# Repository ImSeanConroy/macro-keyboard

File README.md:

# Minimal Layout, Maximum Efficiency

A collection of macro keyboards to boost your productivity without crowding your workspace.

## Features and Development Roadmap

This project is considered complete for the time being, the following outlines the current features and potential future improvements:

### Current Features
- Compact Design: Space-saving with minimal desk footprint.
- Customizable Macros: Assign any key functions to match your workflow.
- Layout Variations: Supports various configurations (e.g., 1x1, 1x2, 1x4, 2x4, and 3x3).

### Future Improvements
- OLED Display: Add and test the inclusion of an OLED display.
- Bluetooth Functionality: Add and test wireless connectivity.
- Custom PCB Design: Move away from prebuilt Seeed Studio development boards. (A previous attempt was made, but limited electronics knowledge made debugging and identifying issues difficult.)

## Getting Started

1. **Open the Project** - Open the `.kicad_pro` file in KiCad to view the project.
2. **Review the Design** - Inspect the schematic and PCB layout to ensure it meets your needs.
3. **Customize or Export** - Make any modifications and export the Gerber files for fabrication.
4. **Order the PCB** - Submit the Gerber files to your preferred PCB manufacturer.
5. **Get the Components** - Purchase the components from the BOM and a compatible board.
6. **3D Print the Case** - Download the STL files for your chosen configuration and print them on a 3D printer.
7. **Assemble the Hardware** - Solder the components and assemble the board and case.
8. **Upload the Firmware** - Connect the board via USB and upload the firmware.

## Required Components

The following are the required components to build any of the macro keyboards:

| Quantity | Component | Description | Source |
| - | - | - | - |
| 1 | Seeed XIAO SAMD21 | Microcontroller board | [PiHut](https://thepihut.com/products/seeed-xiao-samd21?srsltid=AfmBOopsKYftJU7zJh318_QIbgNfs8Iwz2q-IXUMCA7OXGZDiutoXrOy) |
| 12 | Kailh Mechanical Key Switches | Tactile switches | [PiHut](https://thepihut.com/products/kailh-mechanical-key-switches-linear-red-12-pack?variant=40151684677827) |
| 20 | Kailh Switch Sockets | For hot-swapping switches | [PiHut](https://thepihut.com/products/kailh-switch-sockets-for-mx-compatible-mechanical-keys-20-pack?variant=40019715588291) |
| 12 | White DSA Keycaps | Keycap set | [PiHut](https://thepihut.com/products/white-dsa-keycaps-for-mx-compatible-switches-10-pack?variant=40000301301955) |
| 12 | Orange DSA Keycaps | Keycap set | [PiHut](https://thepihut.com/products/orange-dsa-keycaps-for-mx-compatible-switches-10-pack?variant=40000347439299) |
| 10 | Neon Green DSA Keycaps | Keycap set | [PiHut](https://thepihut.com/products/neon-green-dsa-keycaps-for-mx-compatible-switches-10-pack?variant=40000348520643) |

## Contributing

Contributions are welcome. Please open an issue or submit a pull request for any enhancements or bug fixes.

## License

This project is Distributed under the MIT License - see the [LICENSE](LICENSE) file for information.

## Support

If you are having problems, please let me know by [raising a new issue](https://github.com/ImSeanConroy/macro-keyboard/issues/new/choose).

## Acknowledgments

This project was made possible thanks to the following resources:

- [Masterzen's Blog](https://www.masterzen.fr/) - Designing a keyboard from scratch
- [Keyboard Designer Wiki](https://wiki.ai03.com/books/pcb-design/chapter/pcb-designer-guide) - PCB Designer Guide 
- [Seeed Studio Wiki](https://wiki.seeedstudio.com/Seeeduino-XIAO/#resourses) - Getting Started with Seeed Studio XIAO SAMD21

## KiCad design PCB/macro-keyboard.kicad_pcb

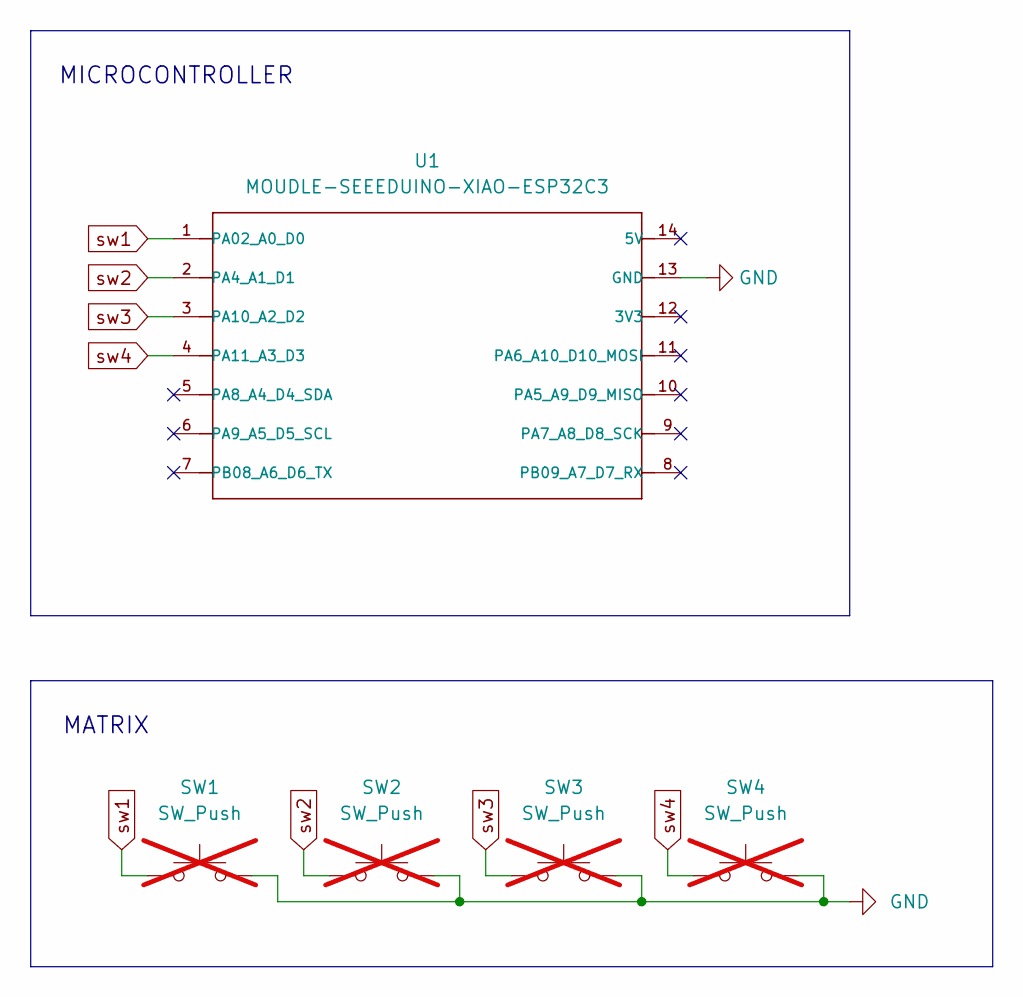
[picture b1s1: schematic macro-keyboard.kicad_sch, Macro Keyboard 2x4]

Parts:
SW1, SW2, SW3, SW4: SW_Push; MXOnly-1U-Hotswap; not fitted
U1: MOUDLE-SEEEDUINO-XIAO-ESP32C3; MOUDLE14P-SMD-2.54-21X17.8MM

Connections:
GND: SW1.2, SW2.2, SW3.2, SW4.2, U1.13 (GND)
sw1: SW1.1, U1.1 (PA02_A0_D0)
sw2: SW2.1, U1.2 (PA4_A1_D1)
sw3: SW3.1, U1.3 (PA10_A2_D2)
sw4: SW4.1, U1.4 (PA11_A3_D3)

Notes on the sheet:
MICROCONTROLLER
MATRIX

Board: 2 copper layers, 5 parts (1 on the bottom side), 5 nets.

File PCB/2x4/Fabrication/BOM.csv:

Id,Designator,Footprint,Quantity,Designation,Supplier and ref
1,"SW2,SW3,SW1,SW4,SW5,SW6,SW8,SW7",MXOnly-1U-Hotswap,8,SW_Push,https://thepihut.com/products/kailh-switch-sockets-for-mx-co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
2,U2,Seeeduino XIAO-MOUDLE14P-2.54-21X17.8MM,1,SeeeduinoXIAO,https://thepihut.com/products/seeed-xiao-samd21?srsltid=AfmB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

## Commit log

2024-11-15 Setup kicad project
2024-11-16 Create schematic
2024-11-18 Update footprint and symbol references
2024-12-30 Layout keycaps
2024-12-31 Layout traces and remove isp header and fours keys
2025-01-09 Update models and add mounting holes
2025-01-13 Add work in progress case for 2x4
2025-01-14 Improve case and convert file to stl
2025-01-14 Improve readme
2025-01-18 Add gerber files
2025-01-22 Add boxes to schematic
2025-02-06 Add missing decoupling capacitor
2025-02-07 Convert to 4 layer board and update traces
2025-06-08 Significantly simplify design
2025-06-12 Add git macros firmware
2025-06-13 Add webex macros firmware
2025-06-13 Add browser and document macros firmware
2025-06-20 Convert to use seeed studio xiao samd21
2025-06-21 Update case for simplified design
2025-06-22 Add varied case configurations
2025-06-27 Add 1x1 and 1x2 pcb design files
2025-06-28 Add 2x4 and 3x3 pcb design files
2025-06-28 Update repo image
2025-06-29 Update firmware
2025-07-02 Fix case usb issue
